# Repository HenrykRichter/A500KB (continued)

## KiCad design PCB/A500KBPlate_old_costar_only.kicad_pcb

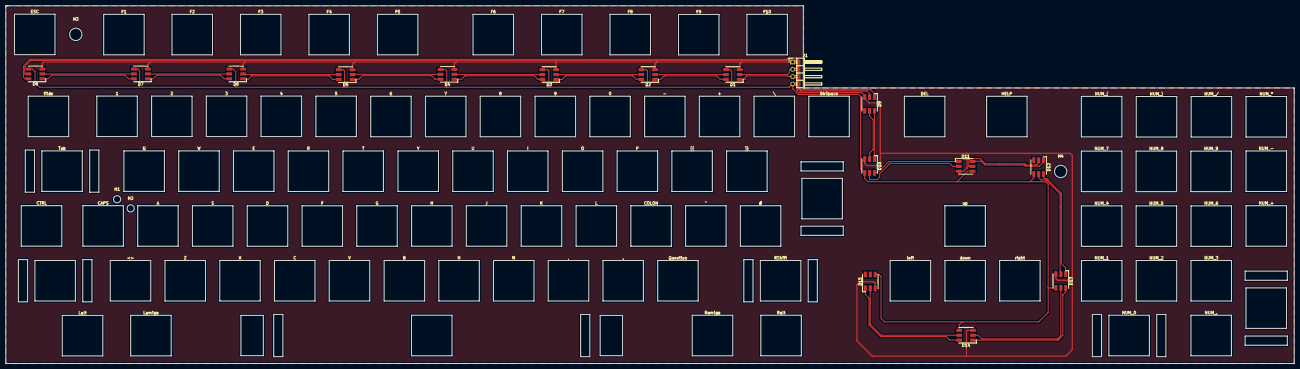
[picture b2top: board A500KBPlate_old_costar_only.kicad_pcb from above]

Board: 2 copper layers, 448.3 x 124.5 mm, 116 parts (0 on the bottom side), 32 nets.

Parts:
D1, D2, D3, D4, D5, D6, D7, D8, D9, D10, D11, D12, D13, D14, D15: APA102; LED_RGB_5050-6
H1, H2: MountingHole; MountingHole_2.5mm
H3, H4: MountingHole; MountingHole_4.3mm_M4
J1: Conn_01x04; PinHeader_1x04_P2.54mm_Horizontal
MX1: ESC; MXMitsumi-1U-PlateCutout
MX2: tilde; MXMitsumi-1.5U-PlateCutout
MX3: Tab; MXMitsumi-2U-PlateCutout
MX4: CTRL; MXMitsumi-1.25U-PlateCutout
MX5: LShift; MXMitsumi-1.75U-PlateCutout
MX6: Lalt; MXMitsumi-1.25U-PlateCutout
MX7: F1; MXMitsumi-1.25U-PlateCutout
MX8: 1; MXMitsumi-1U-PlateCutout
MX9: Q; MXMitsumi-1U-PlateCutout
MX10: CAPS; MXMitsumi-1U-PlateCutout
MX11: <>; MXMitsumi-1U-PlateCutout
MX12: Lamiga; MXMitsumi-1.25U-PlateCutout
MX13: F2; MXMitsumi-1.25U-PlateCutout
MX14: 2; MXMitsumi-1U-PlateCutout
MX15: W; MXMitsumi-1U-PlateCutout
MX16: A; MXMitsumi-1U-PlateCutout
MX17: Z; MXMitsumi-1U-PlateCutout
MX18: F3; MXMitsumi-1.25U-PlateCutout
MX19: 3; MXMitsumi-1U-PlateCutout
MX20: E; MXMitsumi-1U-PlateCutout
MX21: S; MXMitsumi-1U-PlateCutout
MX22: X; MXMitsumi-1U-PlateCutout
MX23: F4; MXMitsumi-1.25U-PlateCutout
MX24: 4; MXMitsumi-1U-PlateCutout
MX25: R; MXMitsumi-1U-PlateCutout
MX26: D; MXMitsumi-1U-PlateCutout
MX27: C; MXMitsumi-1U-PlateCutout
MX28: F5; MXMitsumi-1.25U-PlateCutout
MX29: 5; MXMitsumi-1U-PlateCutout
MX30: T; MXMitsumi-1U-PlateCutout
MX31: F; MXMitsumi-1U-PlateCutout
MX32: V; MXMitsumi-1U-PlateCutout
MX33: Space; MXMitsumi-9U-PlateCutout
MX34: F6; MXMitsumi-1.25U-PlateCutout
MX35: 6; MXMitsumi-1U-PlateCutout
MX36: Y; MXMitsumi-1U-PlateCutout
MX37: G; MXMitsumi-1U-PlateCutout
MX38: B; MXMitsumi-1U-PlateCutout
MX39: F7; MXMitsumi-1.25U-PlateCutout
MX40: 7; MXMitsumi-1U-PlateCutout
MX41: U; MXMitsumi-1U-PlateCutout
MX42: H; MXMitsumi-1U-PlateCutout
MX43: N; MXMitsumi-1U-PlateCutout
MX44: F8; MXMitsumi-1.25U-PlateCutout
MX45: 8; MXMitsumi-1U-PlateCutout
MX46: I; MXMitsumi-1U-PlateCutout
MX47: J; MXMitsumi-1U-PlateCutout
MX48: M; MXMitsumi-1U-PlateCutout
MX49: F9; MXMitsumi-1.25U-PlateCutout
MX50: 9; MXMitsumi-1U-PlateCutout
MX51: O; MXMitsumi-1U-PlateCutout
MX52: K; MXMitsumi-1U-PlateCutout
MX53: ,; MXMitsumi-1U-PlateCutout
MX54: F10; MXMitsumi-1.25U-PlateCutout
MX55: 0; MXMitsumi-1U-PlateCutout
MX56: P; MXMitsumi-1U-PlateCutout
MX57: L; MXMitsumi-1U-PlateCutout
MX58: .; MXMitsumi-1U-PlateCutout
MX59: Ramiga; MXMitsumi-1.25U-PlateCutout
MX60: -; MXMitsumi-1U-PlateCutout
MX61: [{; MXMitsumi-1U-PlateCutout
MX62: COLON; MXMitsumi-1U-PlateCutout
MX63: Question; MXMitsumi-1U-PlateCutout
MX64: Ralt; MXMitsumi-1.25U-PlateCutout
MX65: +; MXMitsumi-1U-PlateCutout
MX66: ]}; MXMitsumi-1U-PlateCutout
MX67: "; MXMitsumi-1U-PlateCutout
MX68: RShift; MXMitsumi-2.75U-PlateCutout
MX69: \; MXMitsumi-1U-PlateCutout
MX70: #; MXMitsumi-1U-PlateCutout
MX71: Return; MXMitsumi-ISO-PlateCutout
MX72: BkSpace; MXMitsumi-1U-PlateCutout
MX73: DEL; MXMitsumi-1.5U-PlateCutout
MX74: left; MXMitsumi-1U-PlateCutout
MX75: up; MXMitsumi-1U-PlateCutout
MX76: down; MXMitsumi-1U-PlateCutout
MX77: HELP; MXMitsumi-1.5U-PlateCutout
MX78: right; MXMitsumi-1U-PlateCutout
MX79: NUM_(; MXMitsumi-1U-PlateCutout
MX80: NUM_7; MXMitsumi-1U-PlateCutout
MX81: NUM_4; MXMitsumi-1U-PlateCutout
MX82: NUM_1; MXMitsumi-1U-PlateCutout
MX83: NUM_0; MXMitsumi-2U-PlateCutout
MX84: NUM_); MXMitsumi-1U-PlateCutout
MX85: NUM_8; MXMitsumi-1U-PlateCutout
MX86: NUM_5; MXMitsumi-1U-PlateCutout
MX87: NUM_2; MXMitsumi-1U-PlateCutout
MX88: NUM_/; MXMitsumi-1U-PlateCutout
MX89: NUM_9; MXMitsumi-1U-PlateCutout
MX90: NUM_6; MXMitsumi-1U-PlateCutout
MX91: NUM_3; MXMitsumi-1U-PlateCutout
MX92: NUM_.; MXMitsumi-1U-PlateCutout
MX93: NUM_*; MXMitsumi-1U-PlateCutout
MX94: NUM_-; MXMitsumi-1U-PlateCutout
MX95: NUM_+; MXMitsumi-1U-PlateCutout
MX96: NUM_ENTER; MXMitsumi-2U-VerticalStabilizers-PlateCutout

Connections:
/+5V: D1.4, D2.4, D3.4, D4.4, D5.4, D6.4, D7.4, D8.4, D9.4, D10.4, D11.4, D12.4, D13.4, D14.4, D15.4, J1.4
/CLK: D1.2, J1.2
/DAT: D1.1, J1.3
/GND: D1.3, D2.3, D3.3, D4.3, D5.3, D6.3, D7.3, D8.3, D9.3, D10.3, D11.3, D12.3, D13.3, D14.3, D15.3, J1.1
unnamed: D1.5, D2.2
unnamed: D1.6, D2.1
unnamed: D2.5, D3.2
unnamed: D2.6, D3.1
unnamed: D3.5, D4.2
unnamed: D3.6, D4.1
unnamed: D4.5, D5.2
unnamed: D4.6, D5.1
unnamed: D5.5, D6.2
unnamed: D5.6, D6.1
unnamed: D6.5, D7.2
unnamed: D6.6, D7.1
unnamed: D7.5, D8.2
unnamed: D7.6, D8.1
unnamed: D8.5, D9.2
unnamed: D8.6, D9.1
unnamed: D9.6, D10.1
unnamed: D9.5, D10.2
unnamed: D10.5, D11.2
unnamed: D10.6, D11.1
unnamed: D11.5, D12.2
unnamed: D11.6, D12.1
unnamed: D12.5, D13.2
unnamed: D12.6, D13.1
unnamed: D13.5, D14.2
unnamed: D13.6, D14.1
unnamed: D14.5, D15.2
unnamed: D14.6, D15.1

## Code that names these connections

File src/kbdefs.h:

/*
  definitions for keyboard and Atmega ports

  requires prior loading of avr headers
*/
#ifndef KBDEFS_H
#define KBDEFS_H

/* LED port, pin as bit index */
#define LEDPORT PORTB
#define LEDDDR  DDRB
#define LEDPIN  7

/* OUTPUT PORT: MAX. 8 BITS */
#define OPORT  PORTA
#define ODDR   DDRA
#define OMASK  0xFC
/* output start bit, output stop bit */ 
#define OSTART (1<<2)
#define OMAX   (1<<7)

/* 6 outputs */
#define OCOUNT 6

/* input ports */
#define ICOUNT 15

/* computer communication port(s) */

#ifdef DEBUG
/* clock on PF2 in DEBUG MODE (IN_LED3) */
#define KBDSEND_CLKP PORTF
#define KBDSEND_CLKD DDRF
#define KBDSEND_CLKB 2
#define KBDSEND_CLKPIN PINF
/* kbdata out on PF3 in DEBUG MODE (IN_LED4) */
#define KBDSEND_SENDP PORTF
#define KBDSEND_SENDD DDRF
#define KBDSEND_SENDB 3
#define KBDSEND_PIN   PINF
#else /* DEBUG */
/* REGULAR */
/* clock on PD2 */
#define KBDSEND_CLKP PORTD
#define KBDSEND_CLKD DDRD
#define KBDSEND_CLKB 2
#define KBDSEND_CLKPIN PIND
/* kbdata out on PD3 */
#define KBDSEND_SENDP PORTD
#define KBDSEND_SENDD DDRD
#define KBDSEND_SENDB 3
#define KBDSEND_PIN  PIND
#endif 

/* special keys (ALT,SHIFT,AMIGA,CTRL) */
#define OCOUNT_SPC 1
#define SPCB_LAMIGA 6
#define SPCB_LALT   5
#define SPCB_LSHIFT 4
#define SPCB_CTRL   3
#define SPCB_RAMIGA 2
#define SPCB_RALT   1
#define SPCB_RSHIFT 0
#define SPCMASK  0x7F /* PB0-PB6 */
#define SPCPORT  PORTB
#define SPCDDR   DDRB
#define SPCPIN   PINB

#if 1
#define KBDSEND_ACKPIN KBDSEND_PIN
#define KBDSEND_ACKB   KBDSEND_SENDB
#else
/* kbd acknowledge input on PB0 (other keyboard) */
#define KBDSEND_ACKP PORTB
#define KBDSEND_ACKD DDRB
#define KBDSEND_ACKPIN PINB
#define KBDSEND_ACKB 0
#endif

/* kbd reset output on PB1 (A500) */
#define KBDSEND_RSTP   PORTD
#define KBDSEND_RSTDDR DDRD
#define KBDSEND_RSTPIN PIND
#define KBDSEND_RSTB 4

/* Reset pin handling: enable/disable pull-up */
#undef PULL_RST /* if pullup is disabled, then we can detect whether the keyboard 
                   is standalone or connected to an A500 */
#ifdef PULL_RST
#define RST_PORTIDLE   KBDSEND_RSTP   |=  (1<<KBDSEND_RSTB); /* pull-up RST */
#else
#define RST_PORTIDLE   KBDSEND_RSTP   &=  ~(1<<KBDSEND_RSTB); /* no pull-up on RST */
#endif

/* spare pads */
#define KBD_SPARE1PORT PORTD
#define KBD_SPARE1DDR  DDRD
#define KBD_SPARE1PIN  PIND
#define KBD_SPARE1B    6

#define KBD_SPARE2PORT PORTD
#define KBD_SPARE2DDR  DDRD
#define KBD_SPARE2PIN  PIND
#define KBD_SPARE2B    7



/* LED sources: Power (analog), Drive, LED3, LED4 */
#define PLED_DDR  DDRF
#define PLED_PORT PORTF
#define PLED_PIN  PINF
#define PLED_BIT 0
#define DRVLED_DDR  DDRF
#define DRVLED_PORT PORTF
#define DRVLED_PIN  PINF
#define DRVLED_BIT 1

/* IN_LED3, IN_LED4 are inactive in debug mode, just use a fake port in that case */
#ifndef DEBUG
#define IN3LED_DDR  DDRF
#define IN3LED_PIN  PINF
#define IN3LED_PORT PORTF
#define IN3LED_BIT 2

#define IN4LED_DDR  DDRF
#define IN4LED_PIN  PINF
#define IN4LED_PORT PORTF
#define IN4LED_BIT 3

#else /* DEBUG */
/* fake ports in debug mode: 4,5 are unused */
#define IN3LED_DDR  DDRF
#define IN3LED_PIN  PINF
#define IN3LED_PORT PORTF
#define IN3LED_BIT 4
#define IN4LED_DDR  DDRF
#define IN4LED_PIN  PINF
#define IN4LED_PORT PORTF
#define IN4LED_BIT 5
#endif /* DEBUG */


#endif /* KBDEFS_H */

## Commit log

2022-01-28 first upload
2022-01-28 picture link
2022-01-31 added Spacebar holder for extra springs, adjusted PCB
2022-02-01 Amiga software: fixed occasional hang
2022-02-01 Primary/Secondary color setting
2022-02-04 PCB update, Amiga software update - finished intended feature set for Amiga software: auto-load from keyboard, some status and error requesters, automatic custom screen if there are not enough availa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
2022-02-04 Makefile without Debug, protocol update - The send protocol from Keyboard to Amiga now includes a length tag such that the host side can copy any data to the internal receive buffer.
2022-02-04 workaround for EEPROM issues
2022-02-20 updates to led.c for keyboard ID
2022-02-23 fixed CLK signal in Sync mode
2022-02-23 Amiga update (reduces warnings with GCC6.x) 3D printed parts for mounting in A3000/A4000 keyboard cases
2022-02-25 updated A2000-4000 reset logic (to immediate hard reset)
2022-03-16 Some more adjustments to Footprints, updated doc
2022-03-16 minor adjustments to main PCB
2022-03-16 added more pictures
2022-03-16 added Licensing information
2022-04-18 finalized V2 design, LED defaults include IN4 now
2022-04-20 adjusted default colors
2022-07-01 preparations for dynamic LED modes
2023-01-19 added additional LED cycling modes to ATMega firmware
2023-03-28 added A500KB Mini, Controller-only variant for Mitsumi Keyboards
2023-08-02 Updated config program and Firmware - improved response when loading config from Keyboard - improved Reset handling of Keyboard
2023-08-18 updated readme for ATMega software
2023-08-19 Amiga program timing adjustments for fast CPUs
2023-09-05 added explicit clock prescaler change to ATMega program - previously, whenever the fuses were not programmed alongside the flash, the Keyboard would run at 2 MHz instead of the intended 16 MHz
2023-09-05 added note about Fuses to README
2023-09-05 changed default state of keyboard matrix output port
2023-09-05 updated firmware - last changes to main.c (output port defaults)
2023-09-06 PCB update - marked some unneeded components N/A - changed LED footprints to fit PLCC LEDs better - moved A500KBMini connector 0.5mm downwards
2023-10-03 reduced global LED power draw fixed Reset handling in unsynchronised state
2023-12-20 added lha of Amiga Utility, updated Mini Gerbers
2024-01-29 Add files via upload
    Added pictures of a build with Cherry Blue switches and vintage A2000 Cherry keycaps.
2024-02-05 LED frame and lens update
2024-02-28 added USB HID mode such that A500KB and A00KBMini work as USB keyboards
2024-06-14 V0.3: improvements for CherryMX builds and fitment - plate design for CherryMX PCB mounted stabilizers (see PCB/A500KBPlate_Gerber_V2D.zip for Costar variant) - PCB modifications for better fitment i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
2024-12-21 V4: optional LED strip on full PCB
2024-12-21 updated LHA to 1.8
2024-12-21 updated Gerbers
2025-01-07 shifted A500KB connectors down on the PCB by 9mm This change allows angled connectors in conjunction with Dupont plugs for connection to the A500 mainboard.
2025-01-07 plate update: 0.5mm more space for stabilizers
2025-01-08 V4c: fixed connector for A2k-A4k keyboard cables
2025-01-12 added auto-detection of connection (A500A3000Uni.hex) - requires R17 on V4c
2025-01-12 Hardware finetuning, Amiga program update
2025-01-13 moved connectors further left to improve clearance
2025-01-14 small bugfix in power-up protocol handling
2025-03-03 Updated Firmware and Amiga tool for BRG LEDs
    - SK9822 support (alongside APA102) for digital LEDs
    - added presets to Amiga program (A500 Red, A500 Green, Test mode)
2025-03-09 updated led_digital.c for RBG modes
2025-03-23 reduced digital LED power usage, added watchdog
2025-03-28 added more presets to Amiga tool
2025-03-28 unified 3D printed parts for internal/external use
2025-03-28 PCB readme update
2025-03-31 added US-Only version (large Return, 2.75U LShift)
2025-04-13 Firmware update: back to 16 MHz, code optimization
2025-04-13 3D printed supports for Checkmate keyboard case
2025-04-21 readme update
2025-12-23 (optional) positioning adapter for CDTV keyboards
2026-01-03 corrected LShift on US version plate gerbers
2026-02-22 added more pictures to illustrate US/INTL layout differences
